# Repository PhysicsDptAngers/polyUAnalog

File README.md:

# polyUAnalog: A Polyphonic Analogic and *Open Source* Synth

## Project Overview

The architecture of polyUAnalog centers around a simple design: a *conductor board* orchestrating multiple *voice boards*. This modular approach allows each board to function independently as a monophonic synthesizer. When combined under the guidance of the conductor board, they form a versatile polyphonic synthesizer capable of operating in various modes:

- **Polyphonic Mode**: Achieve polyphony with up to virtually 120 voices. Our current configuration supports 10 voices of polyphony, tested and functioning seamlessly.
- **Monophonic with Unison and Spread Mode**: For those moments when a single, powerful voice is needed, enhanced with unison and spread capabilities for added depth.
- **Multi-timbral Mode** (Under development as of April 2024): Expanding the synth's versatility by allowing multiple timbres to be played simultaneously.

## Repository Structure

The `polyUAnalog` repository is organized into two main directories, `firmware` and `hardware`, each containing subdirectories dedicated to different components of the synth:

### Firmware
Contains all necessary code to bring the polyUAnalog to life. This includes the microcontroller programming for voice and conductor boards, as well as the controller interface.

- **Voice Board**: The soul of the polyUAnalog's sound, each voice board is an independent monophonic synthesizer.
- **Conductor Board**: The brain behind the operation, orchestrating the voice boards to work in harmony.
- **Controller**: Interface and panel design for hands-on control of the polyUAnalog.

### Hardware
Detailed schematics, PCB designs, and everything required to physically construct the polyUAnalog synth.

- **Voice Board**: Designs and instructions to build each monophonic voice board.
- **Conductor Board**: The blueprint for constructing the central conductor board.
- **Controller**: Panel design and schematics for the physical user interface.

For specific details on each component, please refer to the corresponding `README.md` file within its directory. Our aim is to make the assembly and understanding of the polyUAnalog as accessible as possible.

## Contributing

polyUAnalog thrives on community input and collaboration. Whether you're a seasoned electrical engineer, a software developer with a knack for DSP, or an enthusiast eager to learn and explore, your contributions are welcome. 

## Academic Research and Publications

We have documented our journey and findings in a comprehensive academic paper. This paper delves into the theoretical underpinnings, design choices, and technical challenges encountered during the development of polyUAnalog. While the paper is currently in draft form and distributed as-is, we believe it provides valuable insights into the project's scientific and engineering aspects.

A DOI and access to the official publication will be provided upon acceptance. Additionally, a pre-print version of the paper will be made available to ensure our findings are accessible to the community, fostering further research and development in the field of analog synthesis.

## Sound Examples

We are currently compiling a diverse range of audio samples to showcase the versatility and musicality of polyUAnalog. This is a work in progress, and we appreciate your patience as we curate a collection that truly represents the essence of this project.

Stay tuned for a SoundCloud link, which will be shared here soon. 

## Project Progress

| Task               | Description                                    | Status       |
|--------------------|------------------------------------------------|--------------|
| Documenting    | Drafting an explanation of the synth's electronics and detailing the functionality of the code.      |  In Progress |
| Multitimbral          | Add multitimbral capability by adapting the software.  |  Almost OK ! |
| Faster PID   | Transitioning from the hardware RC-based Timer of the RP2040 to the PIO ones to achieve a faster response time of the DCO waveform.   |  Testing |
| Conductor board | Design and finalize the electronic, PCB, and firmware layout for the conductor board, which enables the control of voice cards, connects to an FX board, and one or multiple controllers.|  Pending |
| FX Loop | Testing the V4220 codec chip.|  Pending |
| Controler | Finishing the first controler : the "basic synth" |  Pending |
| Continous waveform for the DCO | Produce waveform in between saw and triangle and modulate it |  Pending |
| Finishing the paper | Last measurements still to be done |  Pending |

## License

polyUAnalog is open source and distributed under the MIT License.

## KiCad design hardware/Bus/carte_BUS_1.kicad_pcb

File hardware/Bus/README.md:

# BUS Card

## Overview
The **BUS Card** is the interface designed to link multiple voice boards to the Conductor module. 

- **Capacity:** Each BUS board supports up to 4 voice boards.
- **Mounting:** Voice cards are mounted vertically to optimize space.

## Connectivity & Expansion
You can daisychain multiple BUS boards using two different methods:
1. **Ribbon Cable:** Use a standard 2x5 (2.54mm pitch) connector, similar to Eurorack power cables.
2. **Tiling:** Align the boards side-by-side and solder the dedicated edge pads for a rigid connection.

## Input Connector
The pinout and format of the input connector are detailed in the following diagram:

## I2C Addressing
The I2C address is determined by the voltage level at the `ADD_3.3` pad. 

To configure the addressing:
- Install resistors in series between each card.
- Connect the resistor pin of the first card to **GND** (Ground) to complete the voltage divider.
- The resulting voltage drop across the chain assigns a unique hardware address to each board.

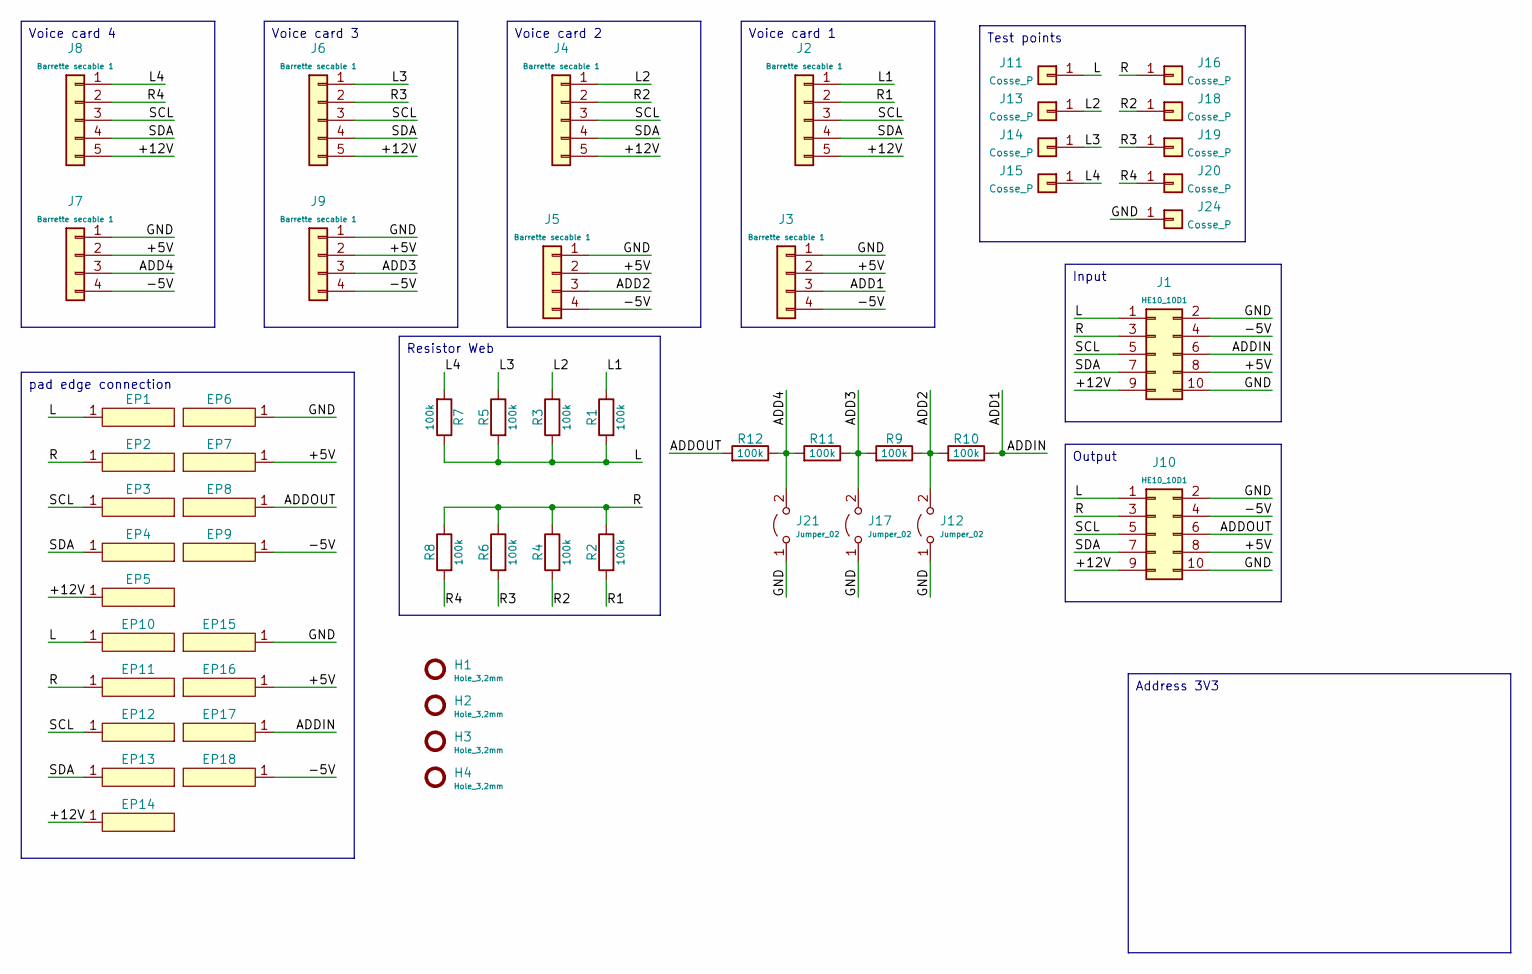
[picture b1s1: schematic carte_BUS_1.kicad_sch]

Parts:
EP1, EP2, EP3, EP4, EP5, EP6, EP7, EP8, EP9, EP10, EP11, EP12, EP13, EP14, EP15, EP16, EP17, EP18: edge_pad
H1, H2, H3, H4: Hole_3,2mm
J1, J10: HE10_10D1; 09185106904
J2, J4, J6, J8: Barrette secable 1; MA01-05
J3, J5, J7, J9: Barrette secable 1; MA01-04
J11, J13, J14, J15, J16, J18, J19, J20, J24: Cosse_P
J12, J17, J21: Jumper_02; MA01-02
R1, R2, R3, R4, R5, R6, R7, R8, R9, R10, R11, R12: 100k; RCMS1206

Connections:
/+5V: EP7.1, EP16.1, J1.8, J3.2, J5.2, J7.2, J9.2, J10.8
/+12V: EP5.1, EP14.1, J1.9, J2.5, J4.5, J6.5, J8.5, J10.9
/-5V: EP9.1, EP18.1, J1.4, J3.4, J5.4, J7.4, J9.4, J10.4
/ADD1: EP17.1, J1.6, J3.3, R10.2
/ADD2: J5.3, J12.2 (B), R9.2, R10.1
/ADD3: J9.3, J17.2 (B), R9.1, R11.2
/ADD4: J7.3, J21.2 (B), R11.1, R12.2
/ADDOUT: EP8.1, J10.6, R12.1
/GND: EP6.1, EP15.1, J1.2, J1.10, J3.1, J5.1, J7.1, J9.1, J10.2, J10.10, J12.1 (A), J17.1 (A), J21.1 (A), J24.1
/L: EP1.1, EP10.1, J1.1, J10.1, J11.1, R1.1, R3.1, R5.1, R7.2
/L1: J2.1, R1.2
/L2: J4.1, J13.1, R3.2
/L3: J6.1, J14.1, R5.2
/L4: J8.1, J15.1, R7.1
/R: EP2.1, EP11.1, J1.3, J10.3, J16.1, R2.2, R4.2, R6.2, R8.2
/R1: J2.2, R2.1
/R2: J4.2, J18.1, R4.1
/R3: J6.2, J19.1, R6.1
/R4: J8.2, J20.1, R8.1
/SCL: EP3.1, EP12.1, J1.5, J2.3, J4.3, J6.3, J8.3, J10.5
/SDA: EP4.1, EP13.1, J1.7, J2.4, J4.4, J6.4, J8.4, J10.7

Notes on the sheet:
Voice card 4
Resistor Web
Voice card 2
Input
Voice card 1
Address 3V3
pad edge connection
Test points
Voice card 3
Output

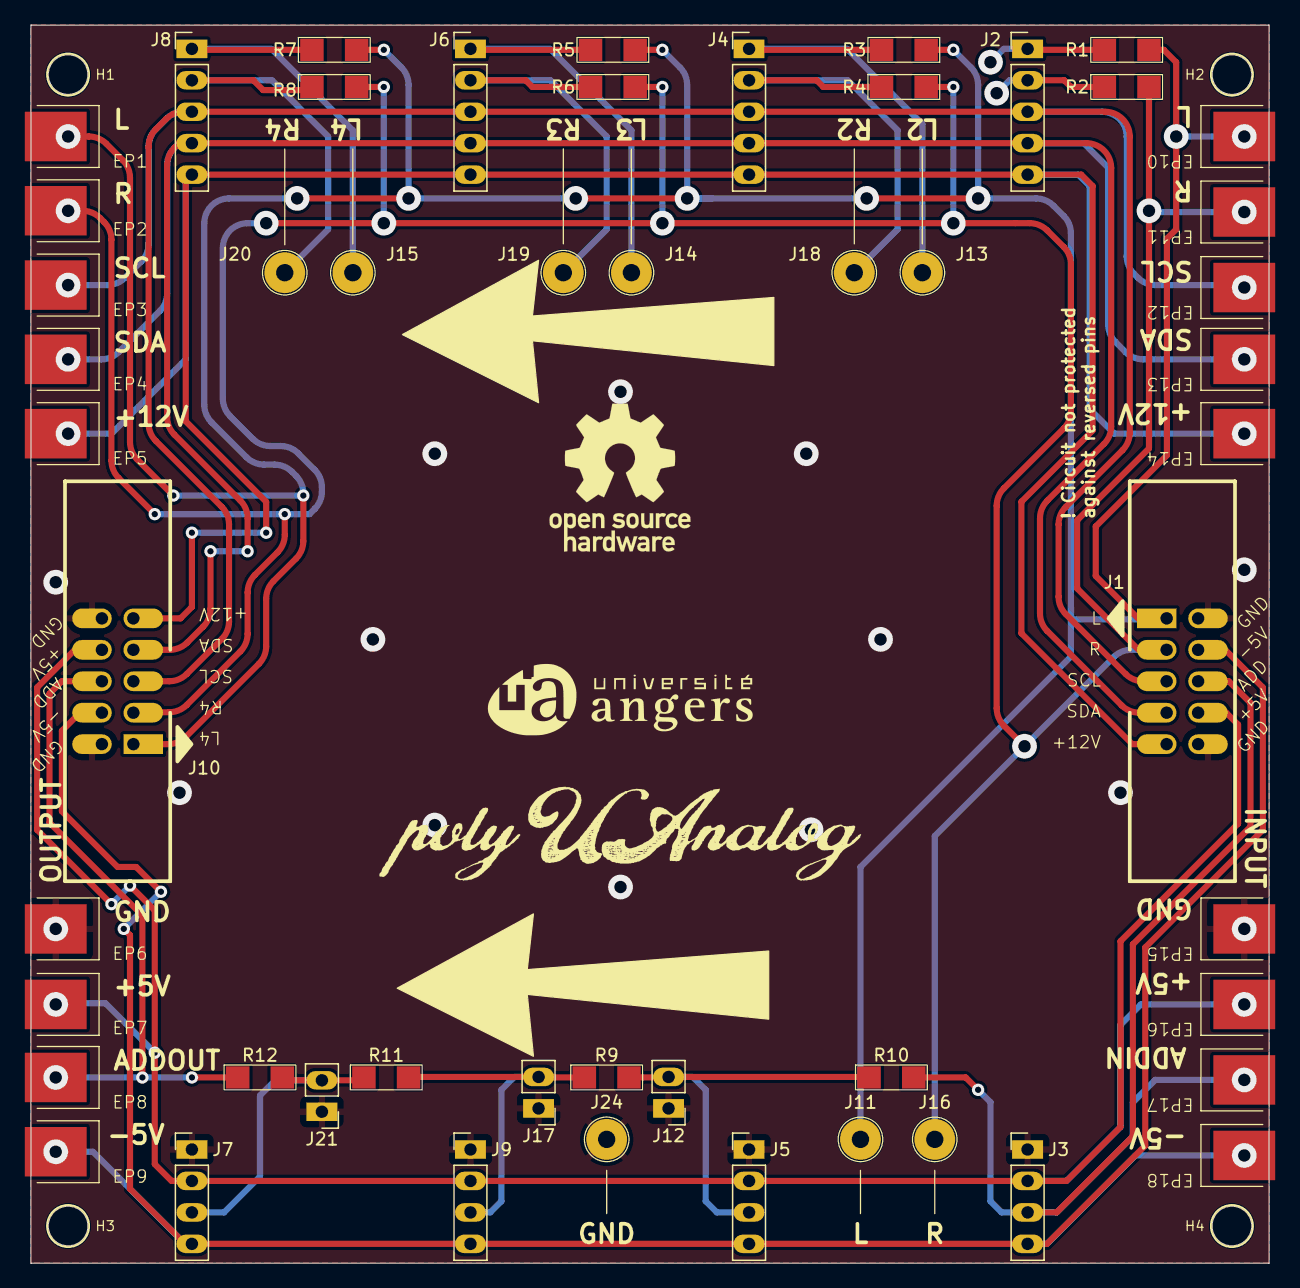
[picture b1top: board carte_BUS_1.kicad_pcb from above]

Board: 2 copper layers, 100.0 x 100.0 mm, 56 parts (0 on the bottom side), 21 nets.

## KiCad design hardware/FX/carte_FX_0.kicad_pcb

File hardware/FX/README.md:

## FX Board

We designed an optional, dedicated FX card based on the **RP2350** microcontroller to handle digital effects. This board connects to the conductor board via a standard 2x5 pin header. Audio input and output data transfer relies on the **I2S protocol**, implemented utilizing the RP2350's Programmable I/O (PIO) blocks.

To accommodate different budgets and assembly constraints, the card supports three ADC and DAC configurations:

* The first approach uses the RP2350's **built-in ADC** paired with a $2 \times 8$-bit PWM-RC filtered DAC for the output.
* The second option employs inexpensive, off-the-shelf **I2S ADC (PCM1808) and DAC (PCM5102A)** modules. While we have included the footprints on the PCB to allow for discrete mounting or to future-proof against discontinued supply, we strongly recommend using the modules themselves.
* The third configuration integrates the **Coolaudio V4220 codec**. This recent and cost-effective chip comes in an SSOP-28 package, making it significantly easier to hand-solder than the QFN packages typical of modern audio codecs. It is worth noting that the V4220 datasheet is poorly documented, as it confusingly mixes specifications from the original Cirrus Logic CS4220 and CS4221 chips it is based on.

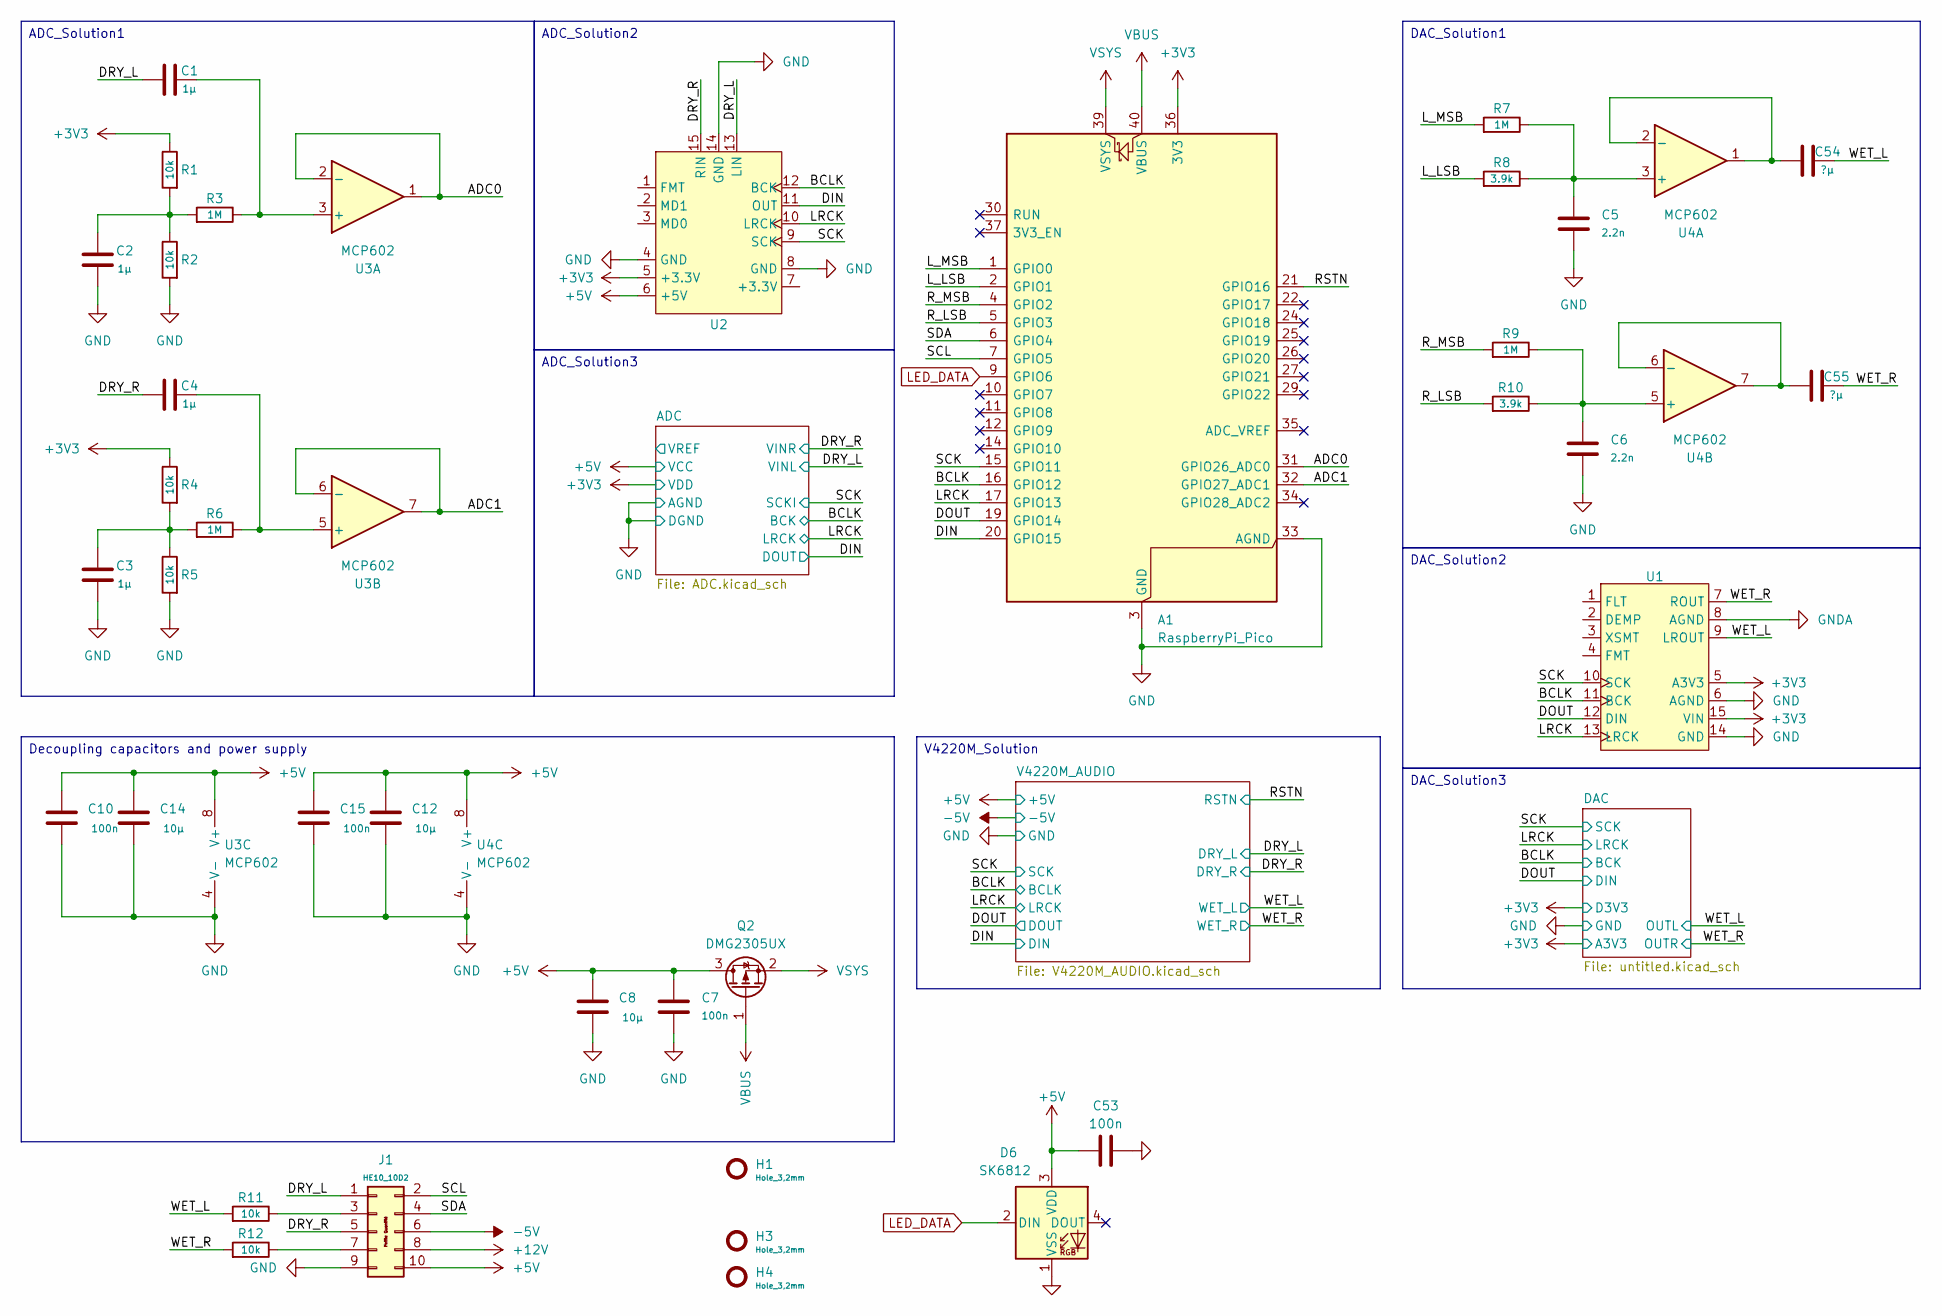
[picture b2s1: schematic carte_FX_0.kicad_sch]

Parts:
A1: RaspberryPi_Pico; RaspberryPi_Pico_Common_Unspecified
C1, C2, C3, C4: 1µ; CCMS1206
C5, C6: 2.2n; CCMS1206
C7, C10, C15: 100n; CCMS1206
C8, C12, C14: 10µ; CCMS1206
C53: 100n; C_0603_1608Metric_Pad1.08x0.95mm_HandSolder
C54, C55: ?µ; CCMS1206
D6: SK6812; LED_SK6812_PLCC4_5.0x5.0mm_P3.2mm
H1, H3, H4: Hole_3,2mm
J1: HE10_10D2; 09185107324
Q2: DMG2305UX; SOT-23
R1, R2, R4, R5, R11, R12: 10k; RCMS1206
R3, R6, R7, R9: 1M; RCMS1206
R8, R10: 3.9k; RCMS1206
U1: PCM_5102a_MOD
U2: PCM1808_MOD
U3, U4: MCP602; SOP-8_3.76x4.96mm_P1.27mm

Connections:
+3V3: A1.36 (3V3), R1.2, R4.2, U1.5 (A3V3), U1.15 (VIN), U2.5 (+3.3V); also elsewhere on the board
+5V: C7.1, C8.2, C10.2, C12.2, C14.2, C15.2, C53.1, D6.3 (VDD), J1.10, Q2.3 (D), U2.6 (+5V), U3.8 (V+), U4.8 (V+); also elsewhere on the board
+12V: J1.8
-5V: J1.6; also elsewhere on the board
/ADC0: A1.31 (GPIO26_ADC0), U3.1, U3.2 (-)
/ADC1: A1.32 (GPIO27_ADC1), U3.6 (-), U3.7
/BCLK: A1.16 (GPIO12), U1.11 (BCK), U2.12 (BCK); also elsewhere on the board
/DIN: A1.20 (GPIO15), U2.11 (OUT); also elsewhere on the board
/DOUT: A1.19 (GPIO14), U1.12 (DIN); also elsewhere on the board
/DRY_L: C1.1, J1.1, U2.13 (LIN); also elsewhere on the board
/DRY_R: C4.1, J1.5, U2.15 (RIN); also elsewhere on the board
/LRCK: A1.17 (GPIO13), U1.13 (LRCK), U2.10 (LRCK); also elsewhere on the board
/L_LSB: A1.2 (GPIO1), R8.1
/L_MSB: A1.1 (GPIO0), R7.1
/RSTN: A1.21 (GPIO16); also elsewhere on the board
/R_LSB: A1.5 (GPIO3), R10.1
/R_MSB: A1.4 (GPIO2), R9.1
/SCK: A1.15 (GPIO11), U1.10 (SCK), U2.9 (SCK); also elsewhere on the board
/SCL: A1.7 (GPIO5), J1.2
/SDA: A1.6 (GPIO4), J1.4
/WET_L: C54.2, R11.1, U1.9 (LROUT); also elsewhere on the board
/WET_R: C55.2, R12.1, U1.7 (ROUT); also elsewhere on the board
GND: A1.3 (GND), A1.8 (GND), A1.13 (GND), A1.18 (GND), A1.23 (GND), A1.28 (GND), A1.33 (AGND), A1.38 (GND), C2.1, C3.1, C5.2, C6.2, C7.2, C8.1, C10.1, C12.1, C14.1, C15.1, C53.2, D6.1 (VSS), J1.9, R2.1, R5.1, U1.6 (AGND), U1.14 (GND), U2.4 (GND), U2.8 (GND), U2.14 (GND), U3.4 (V-), U4.4 (V-); also elsewhere on the board
GNDA: U1.8 (AGND)
LED_DATA: A1.9 (GPIO6), D6.2 (DIN)
unnamed: C2.2, R1.1, R2.2, R3.1
unnamed: C3.2, R4.1, R5.2, R6.1
unnamed: J1.3, R11.2
unnamed: J1.7, R12.2
unnamed: C1.2, R3.2, U3.3 (+)
unnamed: C4.2, R6.2, U3.5 (+)
unnamed: C5.1, R7.2, R8.2, U4.3 (+)
unnamed: C54.1, U4.1, U4.2 (-)
unnamed: C6.1, R9.2, R10.2, U4.5 (+)
unnamed: C55.1, U4.6 (-), U4.7
VBUS: A1.40 (VBUS), Q2.1 (G)
VSYS: A1.39 (VSYS), Q2.2 (S)

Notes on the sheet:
V4220M_Solution
ADC_Solution3
Decoupling capacitors and power supply
ADC_Solution1
DAC_Solution1
DAC_Solution2
DAC_Solution3
ADC_Solution2

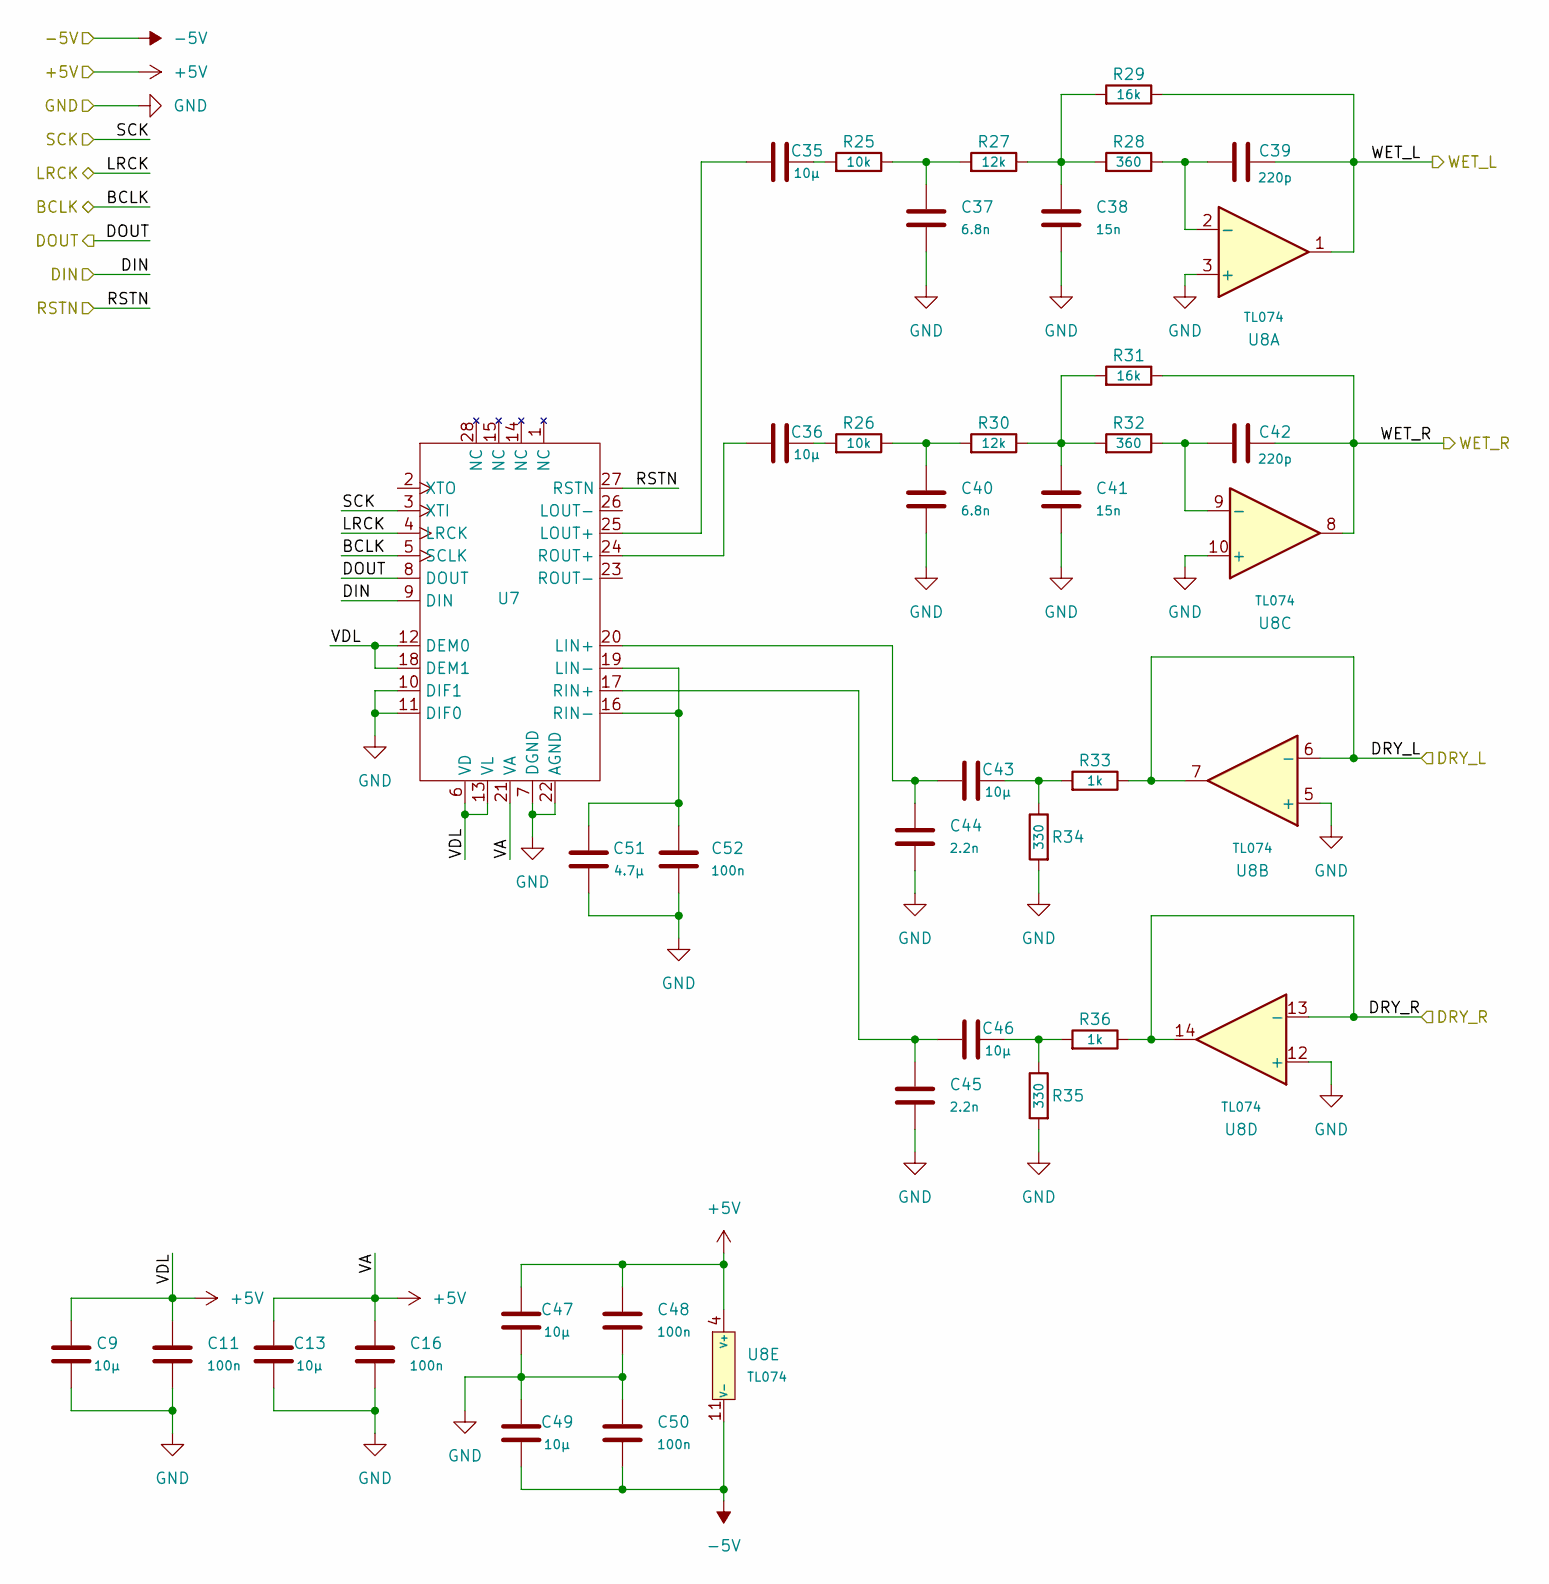
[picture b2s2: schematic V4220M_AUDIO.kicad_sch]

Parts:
C9, C13, C35, C36, C43, C46, C47, C49: 10µ; CCMS1206
C11, C16, C48, C50, C52: 100n; CCMS1206
C37, C40: 6.8n; CCMS1206
C38, C41: 15n; CCMS1206
C39, C42: 220p; CCMS1206
C44, C45: 2.2n; CCMS1206
C51: 4.7µ; CCMS1206
R25, R26: 10k; RCMS1206
R27, R30: 12k; RCMS1206
R28, R32: 360; RCMS1206
R29, R31: 16k; RCMS1206
R33, R36: 1k; RCMS1206
R34, R35: 330; RCMS1206
U7: V4220M
U8: TL074; SOIC-14_3.9x8.7mm_P1.27mm

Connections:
+5V: C9.1, C11.1, C13.1, C16.1, C47.1, C48.1, U7.6 (VD), U7.12 (DEM0), U7.13 (VL), U7.18 (DEM1), U7.21 (VA), U8.4 (V+); also elsewhere on the board
-5V: C49.2, C50.2, U8.11 (V-); also elsewhere on the board
/BCLK: U7.5 (SCLK); also elsewhere on the board
/DIN: U7.9 (DIN); also elsewhere on the board
/DOUT: U7.8 (DOUT); also elsewhere on the board
/DRY_L: R33.2, U8.6 (-), U8.7; also elsewhere on the board
/DRY_R: R36.2, U8.13 (-), U8.14; also elsewhere on the board
/LRCK: U7.4 (LRCK); also elsewhere on the board
/RSTN: U7.27 (RSTN); also elsewhere on the board
/SCK: U7.3 (XTI); also elsewhere on the board
/WET_L: C39.2, R29.2, U8.1; also elsewhere on the board
/WET_R: C42.2, R31.2, U8.8; also elsewhere on the board
GND: C9.2, C11.2, C13.2, C16.2, C37.2, C38.2, C40.2, C41.2, C44.2, C45.2, C47.2, C48.2, C49.1, C50.1, C51.2, C52.2, R34.1, R35.1, U7.7 (DGND), U7.10 (DIF1), U7.11 (DIF0), U7.22 (AGND), U8.3 (+), U8.5 (+), U8.10 (+), U8.12 (+); also elsewhere on the board
unnamed: C35.2, R25.1
unnamed: C36.2, R26.1
unnamed: C37.1, R25.2, R27.1
unnamed: C38.1, R27.2, R28.1, R29.1
unnamed: C40.1, R26.2, R30.1
unnamed: C41.1, R30.2, R31.1, R32.1
unnamed: C43.2, R33.1, R34.2
unnamed: C46.2, R35.2, R36.1
unnamed: C43.1, C44.1, U7.20 (LIN+)
unnamed: C51.1, C52.1, U7.16 (RIN-), U7.19 (LIN-)
unnamed: C35.1, U7.25 (LOUT+)
unnamed: C45.1, C46.1, U7.17 (RIN+)
unnamed: C36.1, U7.24 (ROUT+)
unnamed: C39.1, R28.2, U8.2 (-)
unnamed: C42.1, R32.2, U8.9 (-)

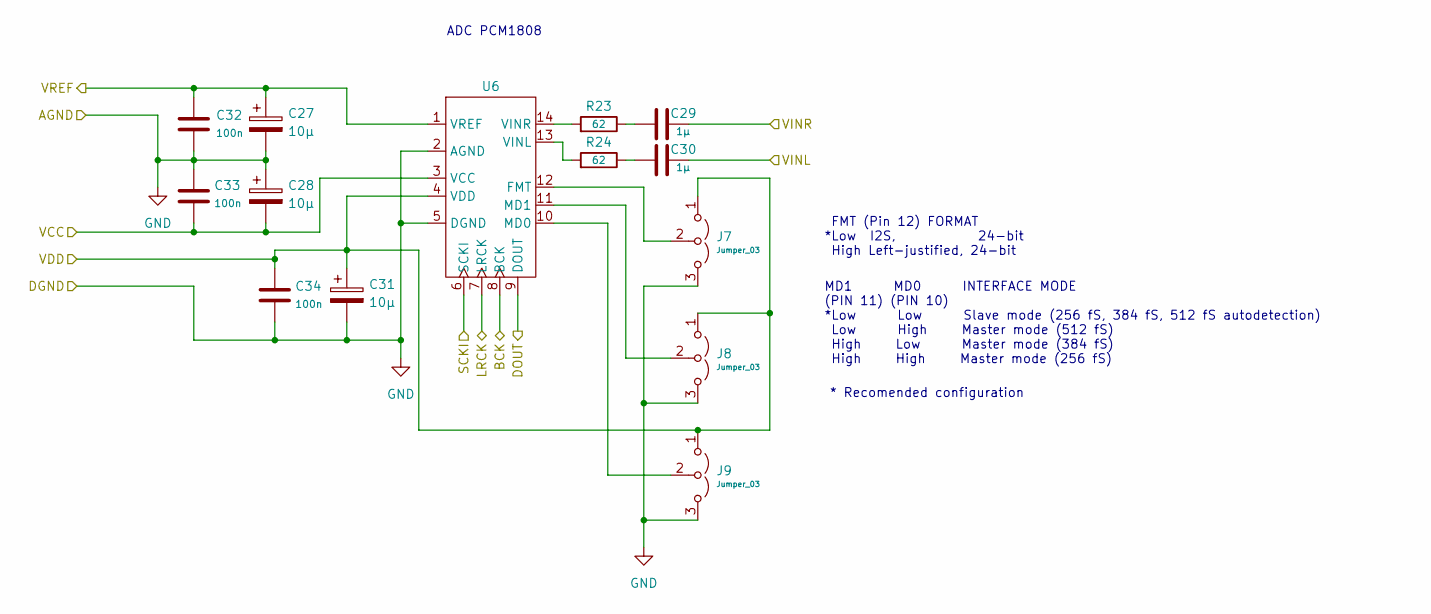
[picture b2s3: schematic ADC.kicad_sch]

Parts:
C27, C28, C31: 10µ; CP_Elec_4x3
C29, C30: 1µ; CCMS1206
C32, C33, C34: 100n; CCMS1206
J7, J8, J9: Jumper_03; MA01-03
R23, R24: 62; RCMS1206
U6: PCM1808

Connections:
+3V3: C31.1, C34.1, J7.1 (A), J8.1 (A), J9.1 (A), U6.4 (VDD); also elsewhere on the board
+5V: C28.2, C33.2, U6.3 (VCC); also elsewhere on the board
/ADC/VREF: C27.1, C32.1, U6.1 (VREF)
/BCLK: U6.8 (BCK); also elsewhere on the board
/DIN: U6.9 (DOUT); also elsewhere on the board
/DRY_L: C30.1; also elsewhere on the board
/DRY_R: C29.1; also elsewhere on the board
/LRCK: U6.7 (LRCK); also elsewhere on the board
/SCK: U6.6 (SCKI); also elsewhere on the board
GND: C27.2, C28.1, C31.2, C32.2, C33.1, C34.2, J7.3 (B), J8.3 (B), J9.3 (B), U6.2 (AGND), U6.5 (DGND); also elsewhere on the board
unnamed: C29.2, R23.2
unnamed: C30.2, R24.2
unnamed: J7.2 (C), U6.12 (FMT)
unnamed: J8.2 (C), U6.11 (MD1)
unnamed: J9.2 (C), U6.10 (MD0)
unnamed: R24.1, U6.13 (VINL)
unnamed: R23.1, U6.14 (VINR)

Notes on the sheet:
* Recomended configuration
MD1 MD0 INTERFACE MODE (PIN 11) (PIN 10) *Low Low Slave mode (256 fS, 384 fS, 512 fS autodetection) Low High Master mode (512 fS) High Low Master mode (384 fS) High High Master mode (256 fS)
ADC PCM1808
FMT (Pin 12) FORMAT *Low I2S, 24-bit High Left-justified, 24-bit

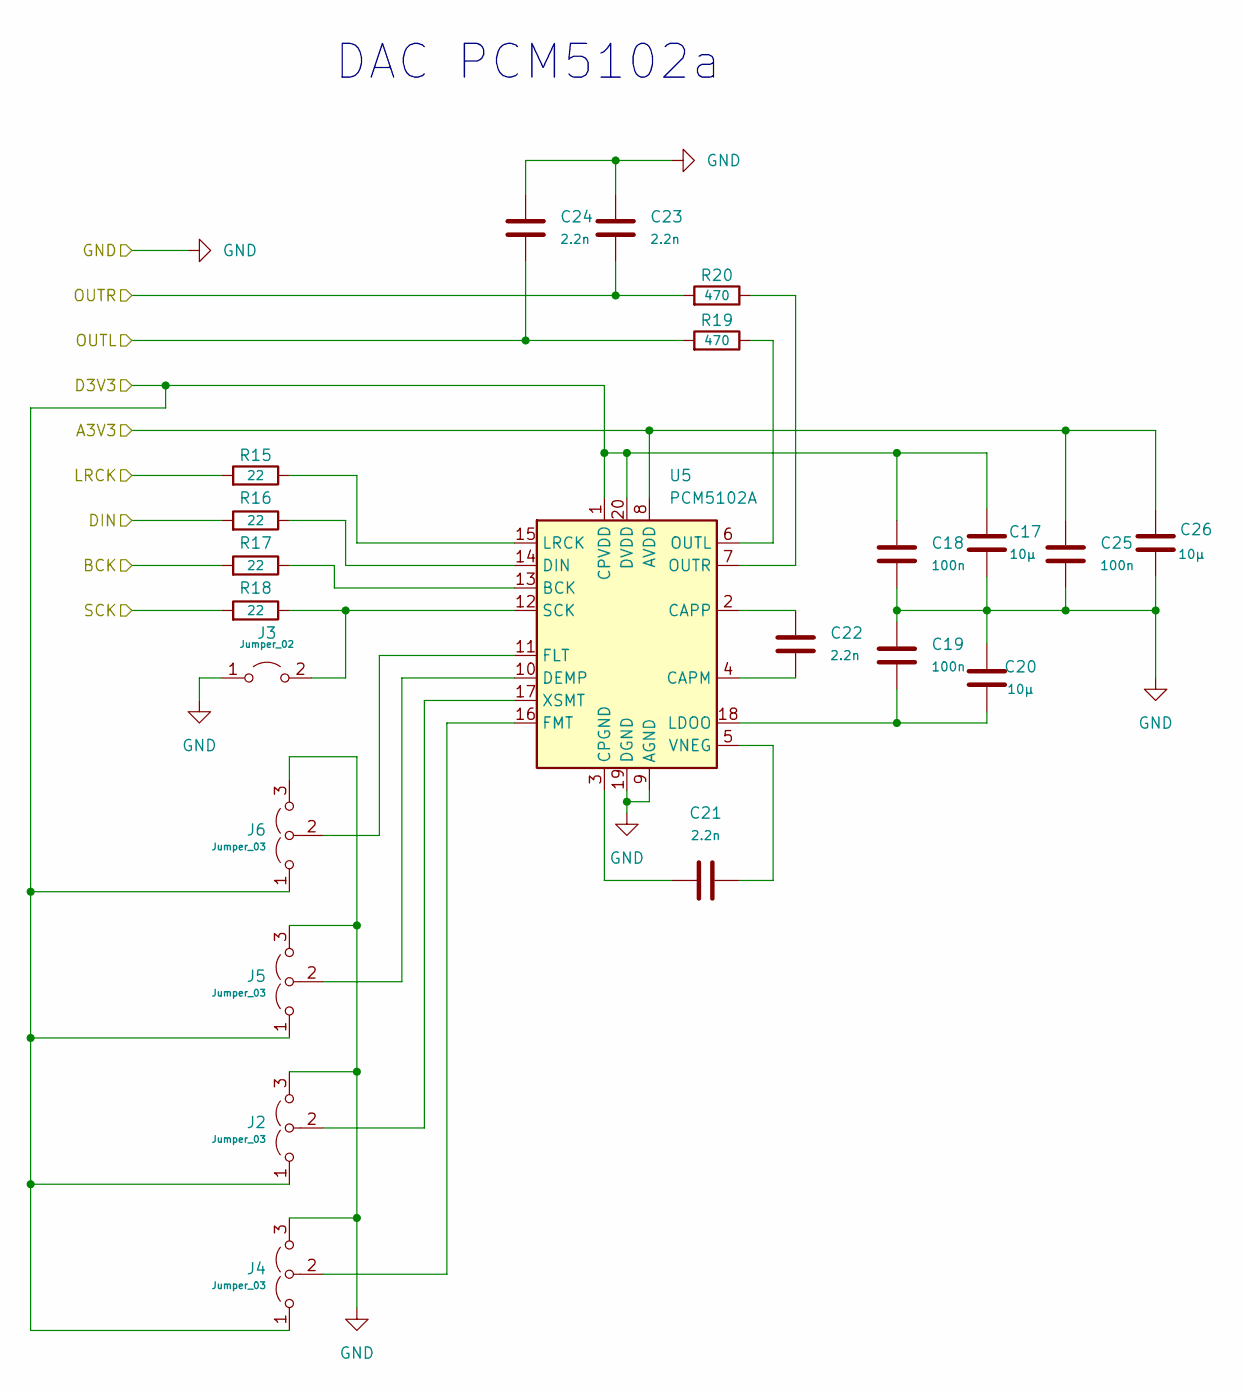
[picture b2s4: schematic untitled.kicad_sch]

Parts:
C17, C20, C26: 10µ; CCMS1206
C18, C19, C25: 100n; CCMS1206
C21, C22, C23, C24: 2.2n; CCMS1206
J2, J4, J5, J6: Jumper_03; MA01-03
J3: Jumper_02; MA01-02
R15, R16, R17, R18: 22; RCMS1206
R19, R20: 470; RCMS1206
U5: PCM5102A; TSSOP-20_4.4x6.5mm_P0.65mm

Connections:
+3V3: C17.2, C18.1, C25.1, C26.2, J2.1 (A), J4.1 (A), J5.1 (A), J6.1 (A), U5.1 (CPVDD), U5.8 (AVDD), U5.20 (DVDD); also elsewhere on the board
/BCLK: R17.1; also elsewhere on the board
/DOUT: R16.1; also elsewhere on the board
/LRCK: R15.1; also elsewhere on the board
/SCK: R18.1; also elsewhere on the board
/WET_L: C24.2, R19.1; also elsewhere on the board
/WET_R: C23.2, R20.1; also elsewhere on the board
GND: C17.1, C18.2, C19.1, C20.2, C23.1, C24.1, C25.2, C26.1, J2.3 (B), J3.1 (A), J4.3 (B), J5.3 (B), J6.3 (B), U5.9 (AGND), U5.19 (DGND); also elsewhere on the board
unnamed: J2.2 (C), U5.17 (XSMT)
unnamed: J3.2 (B), R18.2, U5.12 (SCK)
unnamed: J4.2 (C), U5.16 (FMT)
unnamed: J5.2 (C), U5.10 (DEMP)
unnamed: J6.2 (C), U5.11 (FLT)
unnamed: R17.2, U5.13 (BCK)
unnamed: C22.2, U5.4 (CAPM)
unnamed: C22.1, U5.2 (CAPP)
unnamed: C21.2, U5.3 (CPGND)
unnamed: R16.2, U5.14 (DIN)
unnamed: C19.2, C20.1, U5.18 (LDOO)
unnamed: R15.2, U5.15 (LRCK)
unnamed: R19.2, U5.6 (OUTL)
unnamed: R20.2, U5.7 (OUTR)
unnamed: C21.1, U5.5 (VNEG)

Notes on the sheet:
DAC PCM5102a

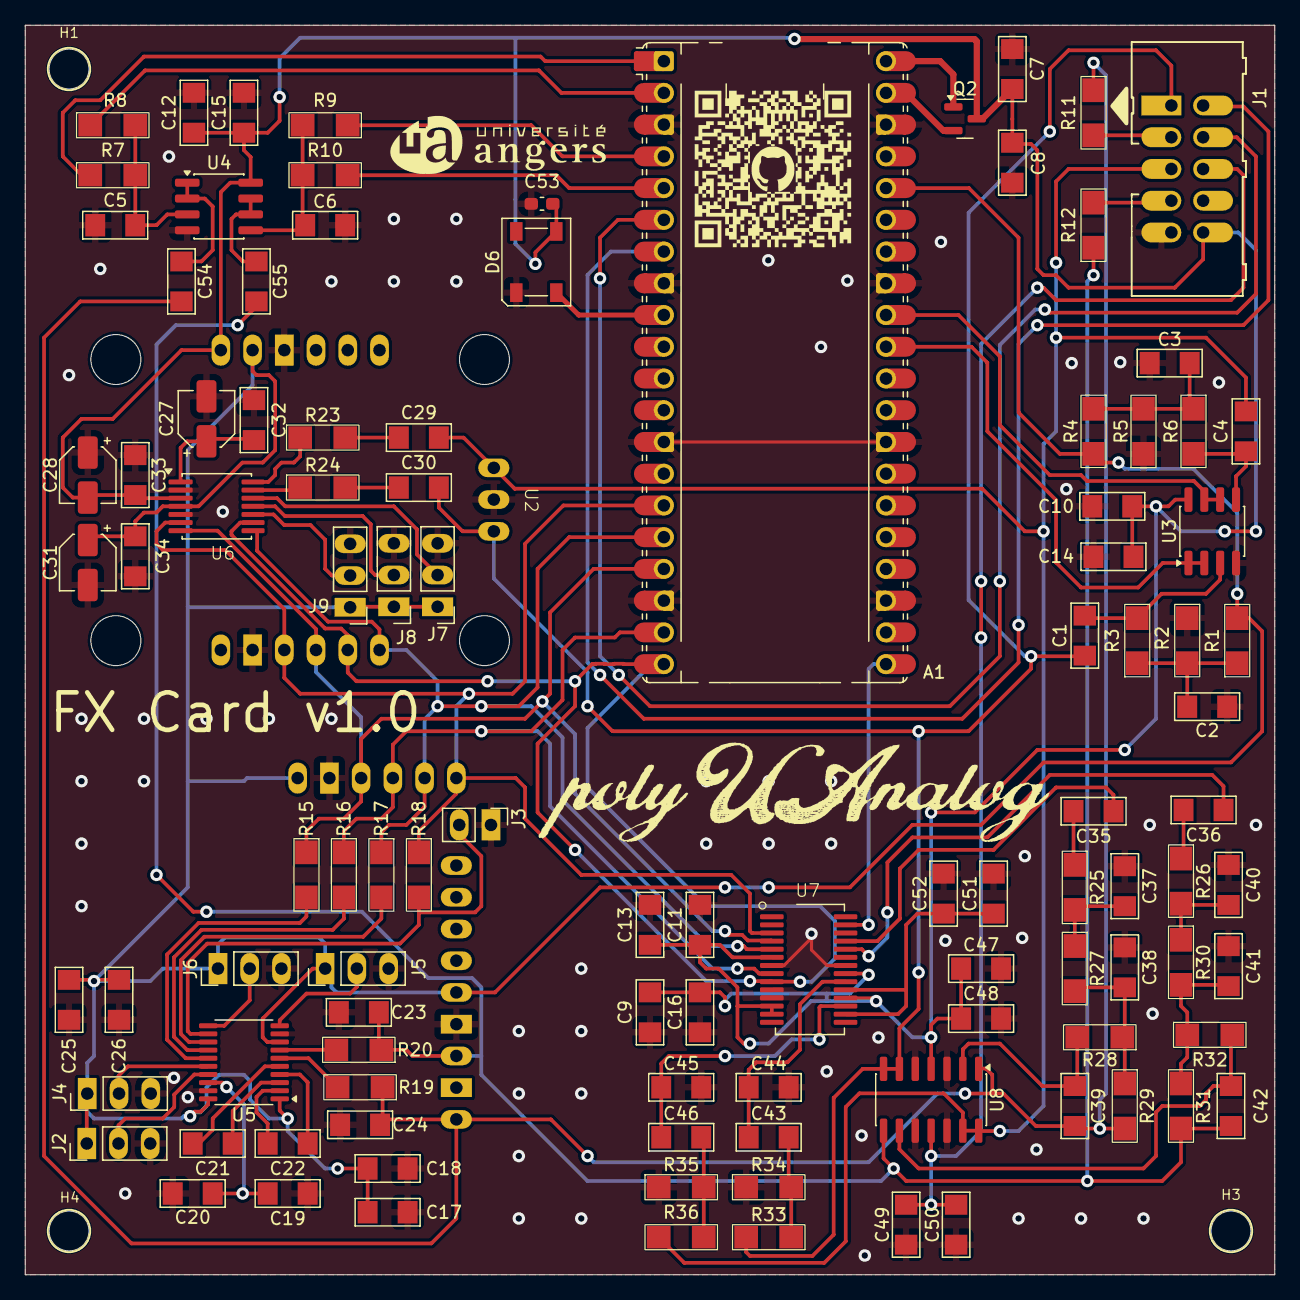
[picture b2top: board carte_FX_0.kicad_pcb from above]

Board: 2 copper layers, 100.0 x 100.0 mm, 110 parts (0 on the bottom side), 73 nets.

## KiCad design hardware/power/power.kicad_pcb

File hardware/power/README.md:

## Power Supply Architecture

The synthesizer requires three voltage rails for proper operation:

- **+12V** rail for the AS3397 chip  
- **+5V** rail for the microcontrollers, various digital ICs, and as the positive supply for the operational amplifiers (OpAmps)  
- **−5V** rail required by the AS3397 and as the negative supply for the OpAmps  

Several strategies have been considered for implementing the power supply. 

In the proposed design, we use a USB-C power supply unit that supports Power Delivery (PD) mode to provide a stable 12V/5A rail. 
	
A buck converter based on the TPS5430 chip, that can easily be obtained as an affordable off-the-shelf module, is used to generate the \SI{+5}{\volt} and \SI{-5}{\volt} rails. With a \SI{3}{\ampere} capacity, this setup is more than sufficient to power both the conductor board and the various voice boards.

Alternative configurations have also been explored:

- In early prototypes, a **compact ATX power supply** was used for +12V and +5V in combination with a **7805** regulator to generate the −5V rail.  
- In the **monophonic version**, the system is powered from a **standard 12V wall adapter** (or a USB-C PD unit), with a 7805 regulator providing the +5V rail, and **charge-pump circuits** used to derive the −5V rail.

Other solutions, such as **off-the-shelf AC-DC modules** from manufacturers like **Meanwell**, may also be considered for increased robustness and ease of integration — particularly when direct connection to the mains is desirable.

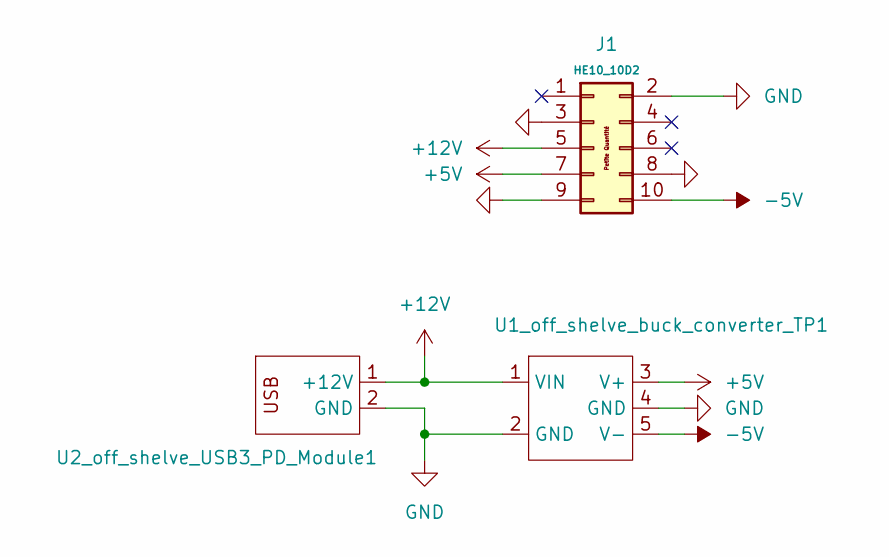
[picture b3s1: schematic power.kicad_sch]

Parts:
J1: HE10_10D2; 09185107324
U1_off_shelve_buck_converter_TP1: XL5430
U2_off_shelve_USB3_PD_Module1: USB_power_delivery_12V

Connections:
+5V: J1.7, U1_off_shelve_buck_converter_TP1.3 (V+)
+12V: J1.5, U1_off_shelve_buck_converter_TP1.1 (VIN), U2_off_shelve_USB3_PD_Module1.1 (+12V)
-5V: J1.10, U1_off_shelve_buck_converter_TP1.5 (V-)
GND: J1.2, J1.3, J1.8, J1.9, U1_off_shelve_buck_converter_TP1.2 (GND), U1_off_shelve_buck_converter_TP1.4 (GND), U2_off_shelve_USB3_PD_Module1.2 (GND)

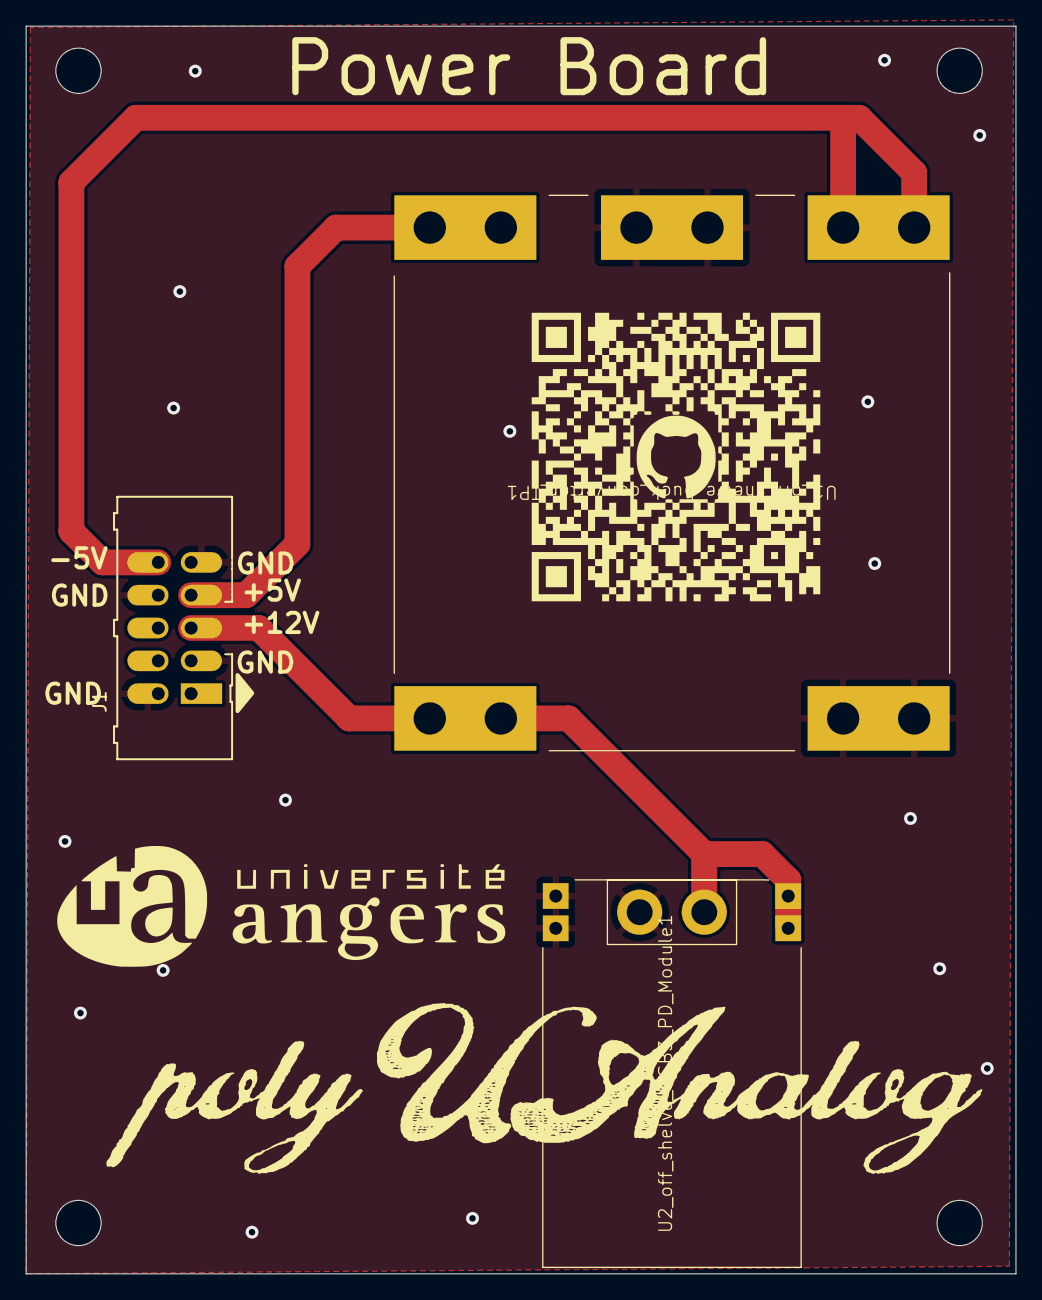
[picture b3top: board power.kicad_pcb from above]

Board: 2 copper layers, 76.6 x 96.6 mm, 3 parts (0 on the bottom side), 4 nets.
